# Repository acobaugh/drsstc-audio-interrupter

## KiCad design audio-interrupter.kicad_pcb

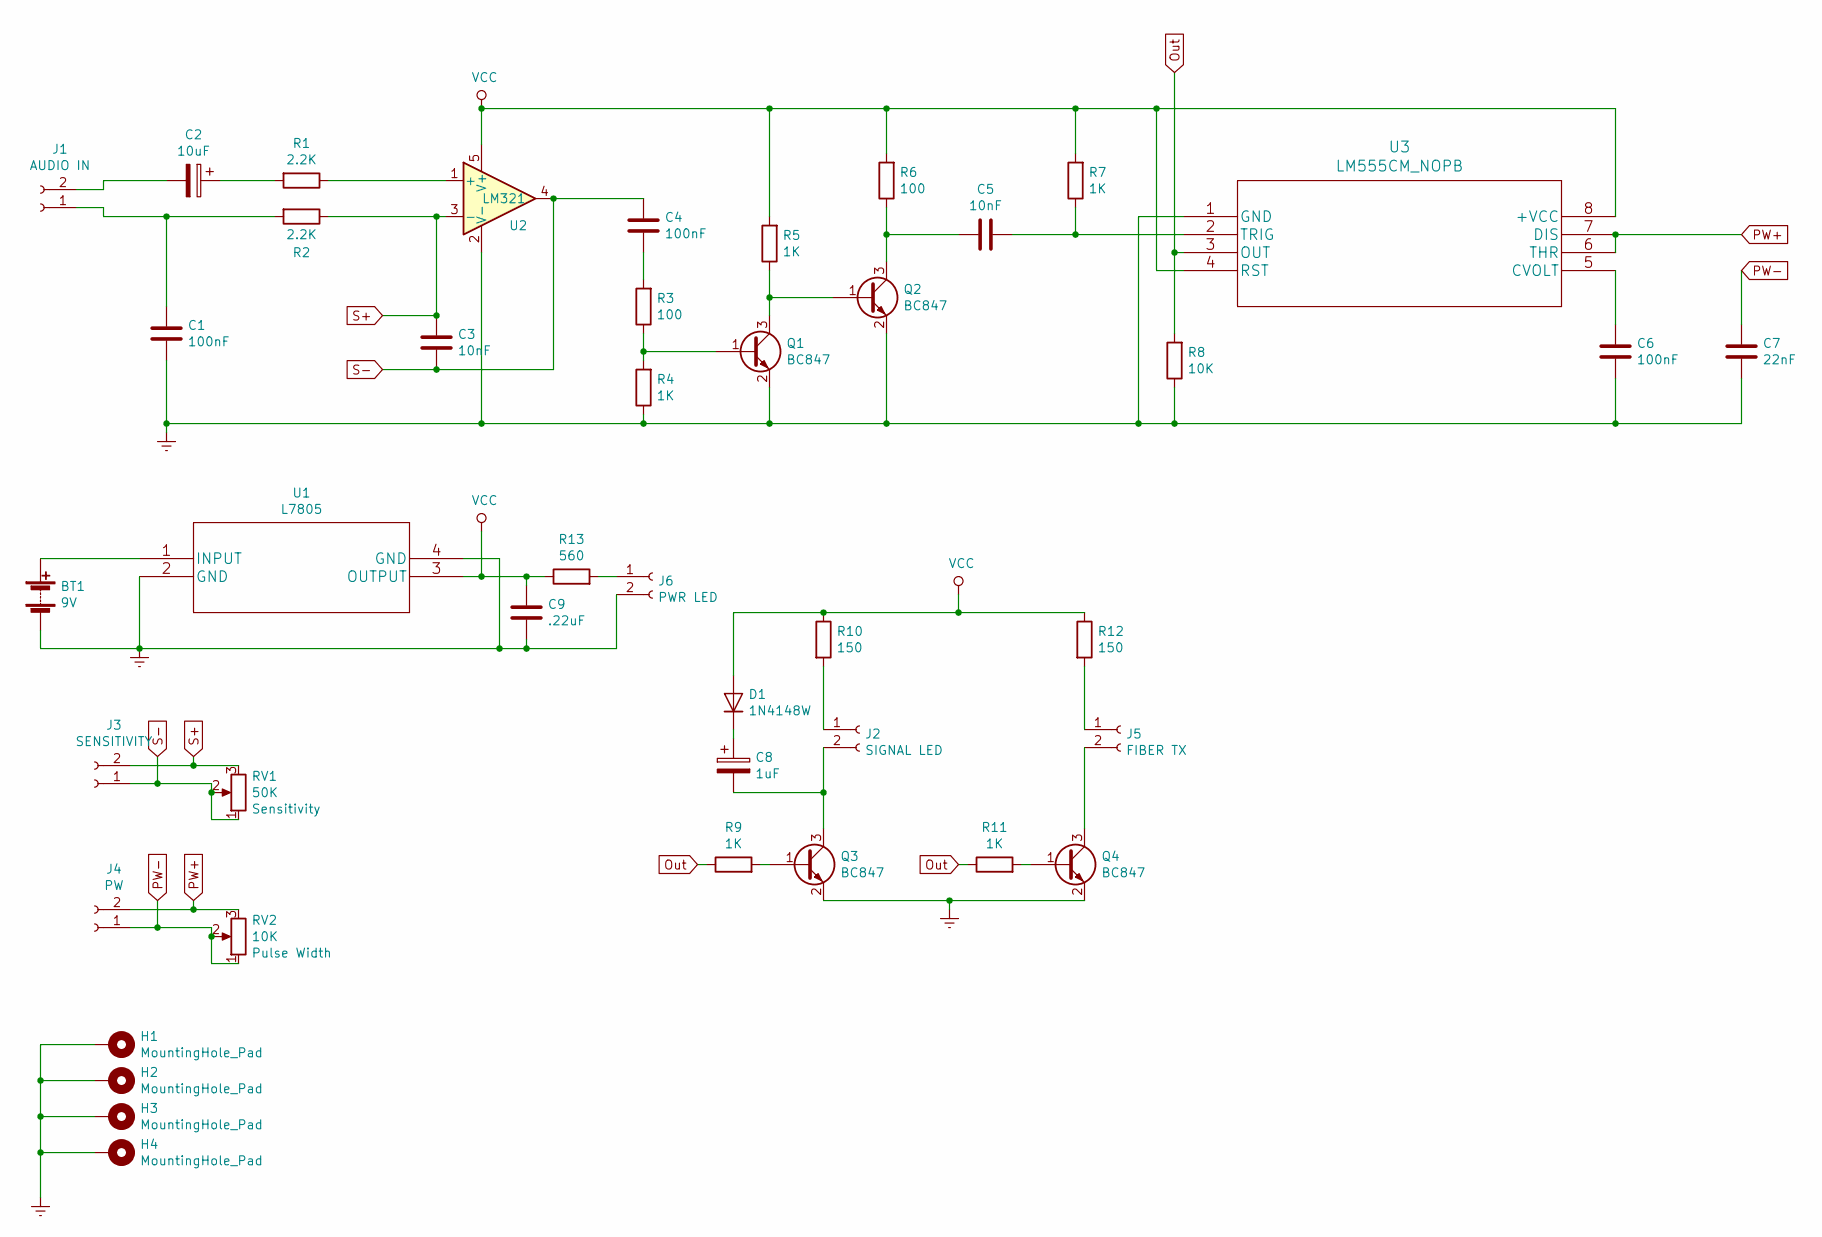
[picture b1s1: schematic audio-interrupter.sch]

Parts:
BT1: 9V; SolderWirePad_1x02_P3.81mm_Drill1mm
C1, C4, C6: 100nF; C_0805_2012Metric_Pad1.15x1.40mm_HandSolder
C2: 10uF; C_1206_3216Metric_Pad1.42x1.75mm_HandSolder
C3, C5: 10nF; C_1206_3216Metric_Pad1.42x1.75mm_HandSolder
C7: 22nF; C_0805_2012Metric_Pad1.15x1.40mm_HandSolder
C8: 1uF; C_1206_3216Metric_Pad1.42x1.75mm_HandSolder
C9: .22uF; C_0805_2012Metric_Pad1.15x1.40mm_HandSolder
D1: 1N4148W; D_SOD-123
H1, H2, H3, H4: MountingHole_Pad; MountingHole_2.5mm_Pad
J1: AUDIO IN; SolderWirePad_1x02_P3.81mm_Drill1mm
J2: SIGNAL LED; SolderWirePad_1x02_P3.81mm_Drill1mm
J3: SENSITIVITY; SolderWirePad_1x02_P3.81mm_Drill1mm
J4: PW; SolderWirePad_1x02_P3.81mm_Drill1mm
J5: FIBER TX; SolderWirePad_1x02_P3.81mm_Drill1mm
J6: PWR LED; SolderWirePad_1x02_P3.81mm_Drill1mm
Q1, Q2, Q3, Q4: BC847; SOT-23
R1, R2: 2.2K; R_0805_2012Metric_Pad1.15x1.40mm_HandSolder
R3: 100; C_0805_2012Metric_Pad1.15x1.40mm_HandSolder
R4, R5, R7, R9, R11: 1K; R_0805_2012Metric_Pad1.15x1.40mm_HandSolder
R6: 100; R_0805_2012Metric_Pad1.15x1.40mm_HandSolder
R8: 10K; R_0805_2012Metric_Pad1.15x1.40mm_HandSolder
R10, R12: 150; R_0805_2012Metric_Pad1.15x1.40mm_HandSolder
R13: 560; R_0805_2012Metric_Pad1.15x1.40mm_HandSolder
RV1: 50K
RV2: 10K
U1: L7805; LM7805MPX&slash_NOPB
U2: LM321; SOT-23-5
U3: LM555CM_NOPB; LM555CM&slash_NOPB

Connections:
Earth: BT1.2 (-), C1.2, C6.2, C7.2, C9.2, H1.1, H2.1, H3.1, H4.1, J6.2, Q1.2 (E), Q2.2 (E), Q3.2 (E), Q4.2 (E), R4.1, R8.1, U1.2 (GND), U1.4 (GND), U2.2 (V-), U3.1 (GND)
unnamed: BT1.1 (+), U1.1 (INPUT)
unnamed: C1.1, J1.1, R2.2
unnamed: C2.1, R1.2
unnamed: C2.2, J1.2
unnamed: C4.2, R3.2
unnamed: C5.1, R7.1, U3.2 (TRIG)
unnamed: C5.2, Q2.3 (C), R6.1
unnamed: C6.1, U3.5 (CVOLT)
unnamed: C8.1, D1.1 (K)
unnamed: C8.2, J2.2, Q3.3 (C)
unnamed: J2.1, R10.2
unnamed: J5.1, R12.2
unnamed: J5.2, Q4.3 (C)
unnamed: J6.1, R13.2
unnamed: Q1.1 (B), R3.1, R4.2
unnamed: Q1.3 (C), Q2.1 (B), R5.1
unnamed: Q3.1 (B), R9.2
unnamed: Q4.1 (B), R11.2
unnamed: R1.1, U2.1 (+)
Out: R8.2, R9.1, R11.1, U3.3 (OUT)
PW+: J4.2, RV2.3, U3.6 (THR), U3.7 (DIS)
PW-: C7.1, J4.1, RV2.1, RV2.2
S+: C3.1, J3.2, R2.1, RV1.3, U2.3 (-)
S-: C3.2, C4.1, J3.1, RV1.1, RV1.2, U2.4
VCC: C9.1, D1.2 (A), R5.2, R6.2, R7.2, R10.1, R12.1, R13.1, U1.3 (OUTPUT), U2.5 (V+), U3.4 (RST), U3.8 (+VCC)

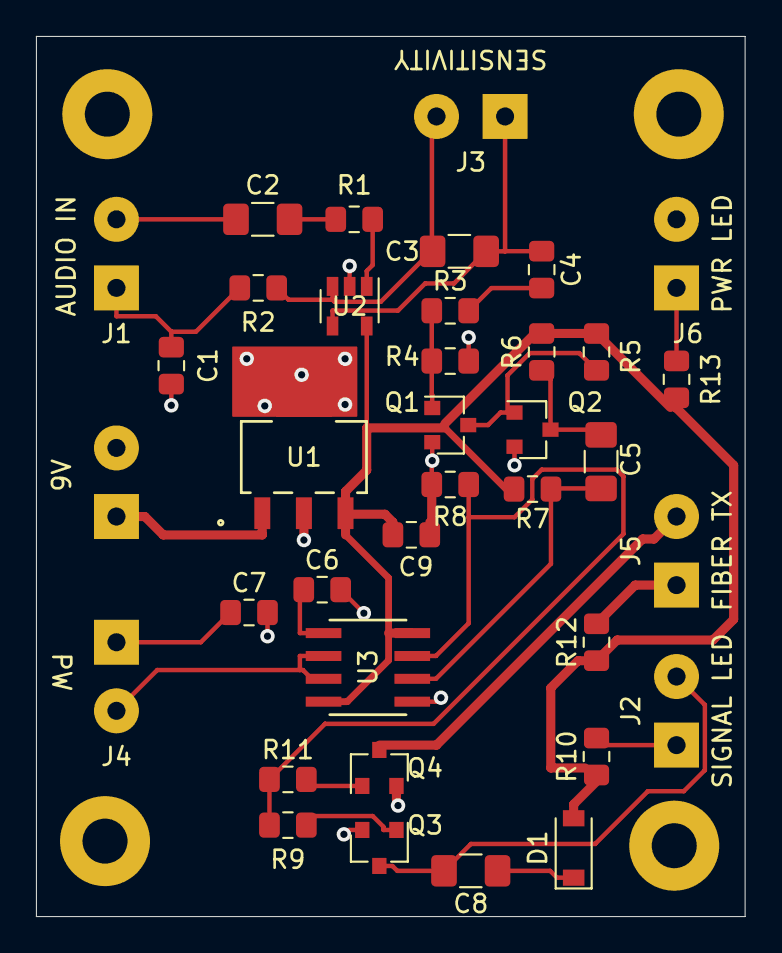
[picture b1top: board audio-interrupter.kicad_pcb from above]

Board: 2 copper layers, 39.4 x 48.9 mm, 41 parts (0 on the bottom side), 26 nets.

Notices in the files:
parts and their libraries:
Copyright 2016 Accelerated Designs. All rights reserved.
